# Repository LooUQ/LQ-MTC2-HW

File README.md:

# LooUQ MTC.2 Hardware

Welcome to the hardware and physical parts repository for the LooUQ MTC.2 Ecosystem. Here you will find resources to aid in your implementation of MTC.2 devices in your design/product. Many parts of the LooUQ MTC.2 ecosystem are available as open-source hardware and there design files are available here. There are also drawings for components that can be 3D printed. 

Software developement tooling is found in the LQ-MTC2-SW repository, which is also found on LooUQ's GitHub site.

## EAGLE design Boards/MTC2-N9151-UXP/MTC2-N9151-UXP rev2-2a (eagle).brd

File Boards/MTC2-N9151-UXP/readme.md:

# MTC2-N9151-UXP
The LooUQ MTC2-N9151 UXplor is a development board providing pin access to all of the MTC2-N9151 signals. It allows for software development, flashing and power monitoring via headers located along the right-hand side of the board. SWD access (debug/flashing) is via a standard 5x2 shrouded header. The UXplor also provide N9151 board power from a USB connection. The VIO voltage can be selected via a jumper at either 3.3v or 1.8v (VDD is fixed at 3.7v). The UXplor also includes a RGB LED the is controlled via a TI constant current control chip on the host extension I2C interface.

You can obtain Zephyr devicetree overlays for the Host Extension interface in order to use the RGB LED with the LooUQ driver. These resources, including the driver, are found in the LooUQ GitHub at https://github.com/LooUQ/LooUQ-MTC2-SW.

You can purchase ready-to-use UXplor boards from LooUQ at https://loouq.com/store.

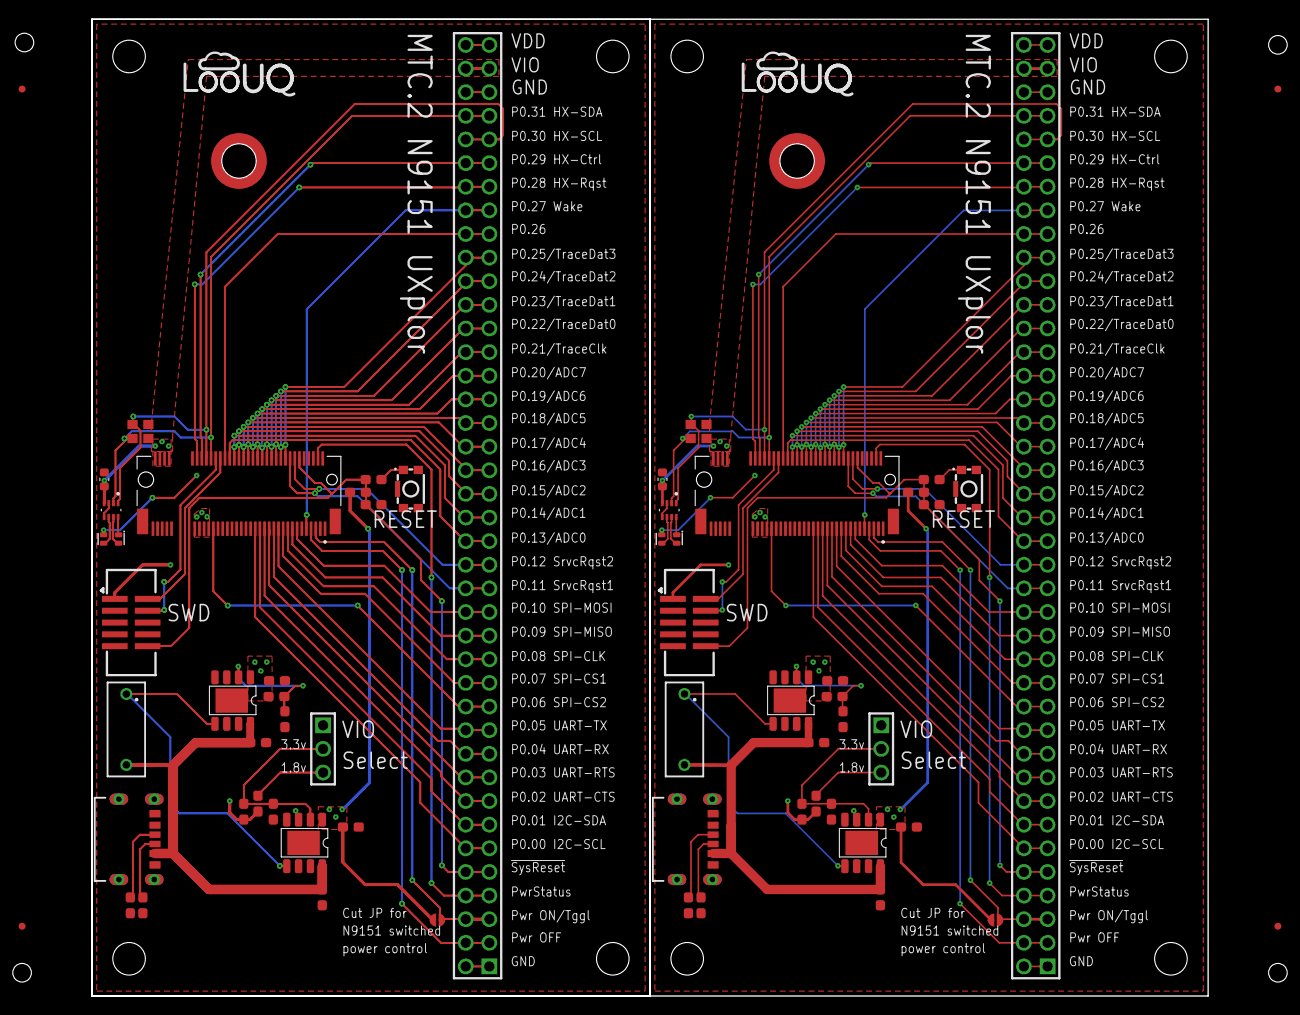
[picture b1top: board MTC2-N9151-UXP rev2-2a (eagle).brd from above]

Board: 2 copper layers, 120.0 x 105.0 mm, 66 parts (0 on the bottom side), 52 nets.

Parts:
C1_1_1, C1_2_1, C2_1_1, C2_2_1, C3_1_1, C3_2_1, C4_1_1, C4_2_1: 4.7uF; CAP_0603
C5_1_1, C5_2_1: 4.7uF; CAP_0603_C5
C6_1_1, C6_2_1: 1uF; CAP_0603_N
D1_1_1, D1_2_1: EAST1616RGBB4; EAST1616RGBB2
FID1, FID2, FID3, FID4: FIDUCIAL; Fiducial
J1_1_1, J1_2_1: CNCTECH 3220-10-0300-00-TR; CnCTech_3220-10-0300-00-TR
J5_1_1, J5_2_1: MTC.2 1-2199230-6 (N9151); TE_1-2199230-6
J8_1_1, J8_2_1: USB4125-GF-A-0190; GCT_USB4125-GF-A-0190_REVA2
J9_1_1, J9_2_1: 90131-0160; HDR-2x40T/2.54x2.54/102x5
J10_1_1, J10_2_1: HDR-1X3T/2.54; HDR-1x3T/2.54/7x2
JP1_1_1, JP1_2_1: CIRCJUMPER-2; Circ-Jumper-2
LG1_1_1, LG1_2_1: LOOUQ LOGO; LooUQ-6mm
MH1_1_1, MH1_2_1: 9774025151R; m.2_standoff
R1_1_1, R1_2_1: 10K; RES_0603
R2_1_1, R2_2_1: 330R; RES_0603_R2
R3_1_1, R3_2_1: 41.7K; RES_0603_R3
R4_1_1, R4_2_1: 62K; RES_0603_R2
R5_1_1, R5_2_1: 73.2K; RES_0603_R5
R6_1_1, R6_2_1: 20K; RES_0603_R6
R7_1_1, R7_2_1: 20K; RES_0603_R5
R8_1_1, R8_2_1, R9_1_1, R9_2_1: 5.1K; RES_0603_R8
R13_1_1, R13_2_1, R14_1_1, R14_2_1: 4.7K; RES_0603_R13
SW1_1_1, SW1_2_1: KMR221GLFS; KMR-2-wG
SW2_1_1, SW2_2_1: 418117270901
U1_1_1, U1_2_1, U2_1_1, U2_2_1: AP7361EA-SPR-13; SO-8EP
U3_1_1, U3_2_1: LP5817DRLR; IC_LP5817DRLR

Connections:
ND_RESETSW: R2_1_1.2, R2_2_1.2, SW1_1_1.1@, SW1_1_1.1@_1, SW1_2_1.1@, SW1_2_1.1@_1
Net_52: J10_1_1.3, J10_2_1.3, R3_1_1.1, R3_2_1.1
Net_Blue: D1_1_1.3, D1_2_1.3, U3_1_1.6, U3_2_1.6
Net_GND: C1_1_1.1, C1_2_1.1, C2_1_1.1, C2_2_1.1, C3_1_1.1, C3_2_1.1, C4_1_1.1, C4_2_1.1, C5_1_1.1, C5_2_1.1, C6_1_1.1, C6_2_1.1, J1_1_1.3, J1_1_1.5, J1_1_1.9, J1_2_1.3, J1_2_1.5, J1_2_1.9, J5_1_1.1, J5_1_1.2, J5_1_1.3, J5_1_1.58, J5_1_1.67, J5_1_1.69, J5_1_1.71, J5_1_1.73, J5_1_1.75, J5_1_1.S1, J5_1_1.S2, J5_2_1.1, J5_2_1.2, J5_2_1.3, J5_2_1.58, J5_2_1.67, J5_2_1.69, J5_2_1.71, J5_2_1.73, J5_2_1.75, J5_2_1.S1, J5_2_1.S2, J8_1_1.A12, J8_1_1.S1, J8_1_1.S2, J8_1_1.S3, J8_1_1.S4, J8_2_1.A12, J8_2_1.S1, J8_2_1.S2, J8_2_1.S3, J8_2_1.S4, J9_1_1.1, J9_1_1.2, J9_1_1.75, J9_1_1.76, J9_2_1.1, J9_2_1.2, J9_2_1.75, J9_2_1.76, R6_1_1.2, R6_2_1.2, R7_1_1.1, R7_2_1.1, R8_1_1.1, R8_2_1.1, R9_1_1.1, R9_2_1.1, SW1_1_1.2@, SW1_1_1.2@_1, SW1_2_1.2@, SW1_2_1.2@_1, U1_1_1.3, U1_2_1.3, U2_1_1.3, U2_2_1.3, U3_1_1.3, U3_1_1.5, U3_2_1.3, U3_2_1.5
Net_Green: D1_1_1.2, D1_2_1.2, U3_1_1.7, U3_2_1.7
Net_PWR-TGL: J5_1_1.5, J5_2_1.5, J9_1_1.5, J9_1_1.6, J9_2_1.5, J9_2_1.6, JP1_1_1.1, JP1_2_1.1
Net_PwrEn: SW2_1_1.1, SW2_2_1.1, U1_1_1.5, U1_2_1.5, U2_1_1.5, U2_2_1.5
Net_Red: D1_1_1.1, D1_2_1.1, U3_1_1.8, U3_2_1.8
Net_SWCLK: J1_1_1.4, J1_2_1.4, J5_1_1.48, J5_2_1.48
Net_SWIO: J1_1_1.2, J1_2_1.2, J5_1_1.46, J5_2_1.46
Net_VBUS: C4_1_1.2, C4_2_1.2, C5_1_1.2, C5_2_1.2, J8_1_1.A9, J8_2_1.A9, SW2_1_1.A1, SW2_2_1.A1, U1_1_1.8, U1_2_1.8, U2_1_1.8, U2_2_1.8
Net_VDD: C2_1_1.2, C2_2_1.2, D1_1_1.4, D1_2_1.4, J5_1_1.51, J5_1_1.53, J5_1_1.55, J5_1_1.57, J5_2_1.51, J5_2_1.53, J5_2_1.55, J5_2_1.57, J9_1_1.79, J9_1_1.80, J9_2_1.79, J9_2_1.80, R5_1_1.2, R5_2_1.2, U1_1_1.1, U1_2_1.1
Net_VIO: C3_1_1.2, C3_2_1.2, C6_1_1.2, C6_2_1.2, J1_1_1.1, J1_2_1.1, J5_1_1.68, J5_1_1.70, J5_1_1.72, J5_1_1.74, J5_2_1.68, J5_2_1.70, J5_2_1.72, J5_2_1.74, J9_1_1.77, J9_1_1.78, J9_2_1.77, J9_2_1.78, JP1_1_1.2, JP1_2_1.2, R1_1_1.2, R1_2_1.2, R3_1_1.2, R3_2_1.2, R4_1_1.2, R4_2_1.2, R13_1_1.2, R13_2_1.2, R14_1_1.2, R14_2_1.2, U2_1_1.1, U2_2_1.1, U3_1_1.4, U3_2_1.4
P0.01_(I2C-SCL): J5_1_1.31, J5_2_1.31, J9_1_1.11, J9_1_1.12, J9_2_1.11, J9_2_1.12
P0.01_(I2C-SDA): J5_1_1.29, J5_2_1.29, J9_1_1.13, J9_1_1.14, J9_2_1.13, J9_2_1.14
P0.02_(UART-CTS): J5_1_1.27, J5_2_1.27, J9_1_1.15, J9_1_1.16, J9_2_1.15, J9_2_1.16
P0.03_(UART-RTS): J5_1_1.25, J5_2_1.25, J9_1_1.17, J9_1_1.18, J9_2_1.17, J9_2_1.18
P0.04_(UART-RX): J5_1_1.23, J5_2_1.23, J9_1_1.19, J9_1_1.20, J9_2_1.19, J9_2_1.20
P0.05_(UART-TX): J5_1_1.21, J5_2_1.21, J9_1_1.21, J9_1_1.22, J9_2_1.21, J9_2_1.22
P0.06_(SPI-CS2): J5_1_1.49, J5_2_1.49, J9_1_1.23, J9_1_1.24, J9_2_1.23, J9_2_1.24
P0.07_(SPI-CS1): J5_1_1.19, J5_2_1.19, J9_1_1.25, J9_1_1.26, J9_2_1.25, J9_2_1.26
P0.08_(SPI-CLK): J5_1_1.17, J5_2_1.17, J9_1_1.27, J9_1_1.28, J9_2_1.27, J9_2_1.28
P0.09_(SPI-MISO): J5_1_1.15, J5_2_1.15, J9_1_1.29, J9_1_1.30, J9_2_1.29, J9_2_1.30
P0.10_(SPI-MOSI): J5_1_1.13, J5_2_1.13, J9_1_1.31, J9_1_1.32, J9_2_1.31, J9_2_1.32
P0.11_(nSrvcRqst1): J5_1_1.16, J5_2_1.16, J9_1_1.33, J9_1_1.34, J9_2_1.33, J9_2_1.34
P0.12_(nSrvcRqst2): J5_1_1.14, J5_2_1.14, J9_1_1.35, J9_1_1.36, J9_2_1.35, J9_2_1.36
P0.13/ADC0: J5_1_1.42, J5_2_1.42, J9_1_1.37, J9_1_1.38, J9_2_1.37, J9_2_1.38
P0.14/ADC1: J5_1_1.40, J5_2_1.40, J9_1_1.39, J9_1_1.40, J9_2_1.39, J9_2_1.40
P0.15/ADC2: J5_1_1.38, J5_2_1.38, J9_1_1.41, J9_1_1.42, J9_2_1.41, J9_2_1.42
P0.16/ADC3: J5_1_1.36, J5_2_1.36, J9_1_1.43, J9_1_1.44, J9_2_1.43, J9_2_1.44
P0.17/ADC4: J5_1_1.34, J5_2_1.34, J9_1_1.45, J9_1_1.46, J9_2_1.45, J9_2_1.46
P0.18/ADC5: J5_1_1.32, J5_2_1.32, J9_1_1.47, J9_1_1.48, J9_2_1.47, J9_2_1.48
P0.19/ADC6: J5_1_1.30, J5_2_1.30, J9_1_1.49, J9_1_1.50, J9_2_1.49, J9_2_1.50
P0.20/ADC7: J5_1_1.28, J5_2_1.28, J9_1_1.51, J9_1_1.52, J9_2_1.51, J9_2_1.52
P0.21/TRACECLK: J5_1_1.26, J5_2_1.26, J9_1_1.53, J9_1_1.54, J9_2_1.53, J9_2_1.54
P0.22/TRACED0: J5_1_1.24, J5_2_1.24, J9_1_1.55, J9_1_1.56, J9_2_1.55, J9_2_1.56
P0.23/TRACED1: J5_1_1.22, J5_2_1.22, J9_1_1.57, J9_1_1.58, J9_2_1.57, J9_2_1.58
P0.24/TRACED2: J5_1_1.20, J5_2_1.20, J9_1_1.59, J9_1_1.60, J9_2_1.59, J9_2_1.60
P0.25/TRACED3: J5_1_1.18, J5_2_1.18, J9_1_1.61, J9_1_1.62, J9_2_1.61, J9_2_1.62
P0.26: J5_1_1.44, J5_2_1.44, J9_1_1.63, J9_1_1.64, J9_2_1.63, J9_2_1.64
P0.27_(Wake): J5_1_1.9, J5_2_1.9, J9_1_1.65, J9_1_1.66, J9_2_1.65, J9_2_1.66
P0.28_(HX-RQST): J5_1_1.56, J5_2_1.56, J9_1_1.67, J9_1_1.68, J9_2_1.67, J9_2_1.68
P0.29_(HX-Ctrl): J5_1_1.54, J5_2_1.54, J9_1_1.69, J9_1_1.70, J9_2_1.69, J9_2_1.70
P0.30_HX-SCL: J5_1_1.52, J5_2_1.52, J9_1_1.71, J9_1_1.72, J9_2_1.71, J9_2_1.72, R14_1_1.1, R14_2_1.1, U3_1_1.1, U3_2_1.1
P0.31_HX-SDA: J5_1_1.50, J5_2_1.50, J9_1_1.73, J9_1_1.74, J9_2_1.73, J9_2_1.74, R13_1_1.1, R13_2_1.1, U3_1_1.2, U3_2_1.2
PUSB_CC1: J8_1_1.A5, J8_2_1.A5, R9_1_1.2, R9_2_1.2
PUSB_CC2: J8_1_1.B5, J8_2_1.B5, R8_1_1.2, R8_2_1.2
PWR-OFF: J5_1_1.7, J5_2_1.7, J9_1_1.3, J9_1_1.4, J9_2_1.3, J9_2_1.4
Status-ON/OFF: J5_1_1.4, J5_2_1.4, J9_1_1.7, J9_1_1.8, J9_2_1.7, J9_2_1.8
VDD_FB: R5_1_1.1, R5_2_1.1, R6_1_1.1, R6_2_1.1, U1_1_1.2, U1_2_1.2
VIO_FB: J10_1_1.2, J10_2_1.2, R4_1_1.1, R4_2_1.1, R7_1_1.2, R7_2_1.2, U2_1_1.2, U2_2_1.2
nSysReset: C1_1_1.2, C1_2_1.2, J1_1_1.10, J1_2_1.10, J5_1_1.12, J5_2_1.12, J9_1_1.9, J9_1_1.10, J9_2_1.9, J9_2_1.10, R1_1_1.1, R1_2_1.1, R2_1_1.1, R2_2_1.1

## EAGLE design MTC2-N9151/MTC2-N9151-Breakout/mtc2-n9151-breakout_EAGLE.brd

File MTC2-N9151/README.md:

# LooUQ MTC2-N9151

The LooUQ MTC2-N9151 is our flagship modem based on the Nordic Semiconductor nRF9151 System-in-Package (SIP) device. Nordic's [documentation](https://docs.nordicsemi.com/category/nrf9151-category) about the nRF9151 SIP is relevant the our MTC2-N9151 modem. LooUQ has done the work to package the nRF9151 SIP into a convenient PCB form to make incorporation into your device as straight forward as possible.

The [MTC.2 Interface Guide](https://drive.google.com/file/d/1XxZAA_1KvOwKZDBlQWn0SYPFL24nAV9U/view?usp=drive_link) discusses the steps to incorporate the N9151 into your product/project. 
* The physical characteristics of mounting the N9151 in your host system
* The electrical requirements needed by the N9151
* The signals to/from the N9151 and it's host

*LooUQ software developement tooling is found in the [LQ-MTC2-SW](https://github.com/LooUQ/LooUQ-MTC2-SW) repository (also found on LooUQ's GitHub site). This includes resources for Nordic Connect SDK like board definition files and sample applications.*

# What You Need
To work with the MTC2-N9151 you will need some things at hand.
* Microsoft [Visual Studio Code](https://code.visualstudio.com/) code editor
* Nordic's [Nordic NRF Connect](https://www.nordicsemi.com/Products/Development-tools/nRF-Connect-for-Desktop?utm_feeditemid=&utm_device=c&utm_term=nrf54l15&utm_source=google&utm_medium=ppc&utm_campaign=nRF54L15&hsa_cam=21894111243&hsa_grp=177111642664&hsa_mt=b&hsa_src=g&hsa_ad=720961843386&hsa_acc=1116845495&hsa_net=adwords&hsa_kw=nrf54l15&hsa_tgt=kwd-2316120203756&hsa_ver=3&gad_source=1&gad_campaignid=21894111243&gbraid=0AAAAADPygHJwnoNPRfWQ0ravOUsDLXLXU&gclid=CjwKCAiA24XJBhBXEiwAXElO39W5oalXI05StjYgUkkjHeaIkVXiZc4hHY8_mm-0arYAEs6eRHNuhhoClUkQAvD_BwE) extension for VS Code
* Nordic's [nRF Connect for Desktop](https://www.nordicsemi.com/Products/Development-tools/nRF-Connect-for-Desktop?utm_feeditemid=&utm_device=c&utm_term=nrf54l15&utm_source=google&utm_medium=ppc&utm_campaign=nRF54L15&hsa_cam=21894111243&hsa_grp=177111642664&hsa_mt=b&hsa_src=g&hsa_ad=720961843386&hsa_acc=1116845495&hsa_net=adwords&hsa_kw=nrf54l15&hsa_tgt=kwd-2316120203756&hsa_ver=3&gad_source=1&gad_campaignid=21894111243&gbraid=0AAAAADPygHJwnoNPRfWQ0ravOUsDLXLXU&gclid=CjwKCAiA24XJBhBXEiwAXElO39W5oalXI05StjYgUkkjHeaIkVXiZc4hHY8_mm-0arYAEs6eRHNuhhoClUkQAvD_BwE) (optional, but highly recommended)
* A SWD debugging probe (Segger J-Link recommended)
* A MTC.2 host providing connections and power (see LooUQ's offerings below, available in our online store)
* A MTC2-N9151 *(of course you will need one or more of these)*
* Antenna(s) 
    * Depending on your use case you will need a cellular antenna for LTE/DECT-NR+ and a GNSS antenna for GNSS/GPS location determination.

## Using LooUQ Development hosts
LooUQ has two development hosts available to make getting started with the MTC2-N9151 a straight forward process: the MTC2-N9151-BRK (breakout board) and the MTC2-N9151-UXP (UXplor host). With either of these two boards, you can get started developing applications for the N9151. They are physically the same size and have identical peripheral header pin configurations.

### MTC2-N9151-Breakout
The N9151 breakout board is simply that, a breakout, exposing all the signals to/from the MTC2-N9151 modem device. Connections for external power, nRF9151 reset, SWD (flash/debug) and all peripheral pins (GPIO, I2C, SPI, UART, etc.). The breakout is designed to be simple and stay out of the way, providing only the essentials for flashing and debugging your N9151 applications.

### MTC2-N9151-UXplor
The N9151 UXplor is the breakout PLUS handy other functionality. The UXplor has a USB connector that sources power via integrated regulators. There is a VDD regulator delivery 3.8v and a VIO regulator that can be set for 3.3v or 1.8v. There is also a RGB LED indicator, the RBG controller is from TI and is I2C-connected. LooUQ provides a driver for LED controller, which is available in the LooUQ-MTC2-SW software repository.

## Creating MTC2-N9151 Applications
If you are new to ***Nordic nRF Connect*** consider investing time in completing one or more of the fine online courses at the [Nordic Developer Academy](https://academy.nordicsemi.com/). If you already have nRF Connect development experience, head over to the [software repository](https://github.com/LooUQ/LooUQ-MTC2-SW) and check out the information there. We have board definitions, samples, and driver code ready for your use. 

## Creating Your Own MTC2-N9151 Host 
LooUQ uses DipTrace as our PCB design suite. It has a complete set of tools for schematic creation, PCB layout, and maintaining component libraries. For information about DipTrace and how to use it see...[Get Diptrace](https://diptrace.com/). LooUQ has been using DipTrace as our electronics design tool since 2016 and we are proud to proclaim it's virtues: reasonable cost, wide support, comprehensive set of tooling; give it a try.

Given that there are multiple tools out there for PCB design/develoment, LooUQ is sharing our open-hardware designs in both DipTrace and Eagle formats. Eagle is a widely supported format for schematic and PCB board layouts. Both of the host boards above are available in the Boards folder of this repository. Depending on your needs either could be a good starting point for integration into your project.

Nordic documentation about the nRF9151 SIP applies to the LooUQ MTC2-9151; all limits should be observed. The MTC2-N9151 will draw slightly more power depending on operating state. GNSS has power draw for either the on-board LNA chip and optionally the external LNA power injection circuit. The N9151 also has 2 LEDs (power-green, network-blue), which can be individually disabled by cutting a jumper. LooUQ can deliver the MTC2-N9151 with custom LNA or LED configurations (note MOQ is required).

### Interfacing to the N9151
* Physical layout
* Power
    * VDD: 3.0v - 5.5v (LooUQ has observed that when VDD is above 4.5v, a VIO of 1.8v has issues)
    * VIO: 1.7v to 3.6v
    * The UXplor VDD is 3.8v and VIO is selectable at 3.3v or 1.8v
* Flash/debug requires connectivity to the 2 SWD pins (both the Breakout and UXplor expose these signals to a 10-pin Cortex header)
* Both LTE/DECT and GNSS antennas are directly connected to the MTC2-N9151 via U.FL connectors

**Host Physical Board Layout**
The physical connection between the MTC2-N9151 and the host PCB is accomplished with 3 parts in the configuration below.
* TE 1-2199230-6 (M.2 Key-M)
* Wurth 9774025151R (M2.5 stand-off, soldered)
* 2.5M x 8mm hex head bolt (fully-threaded, course)

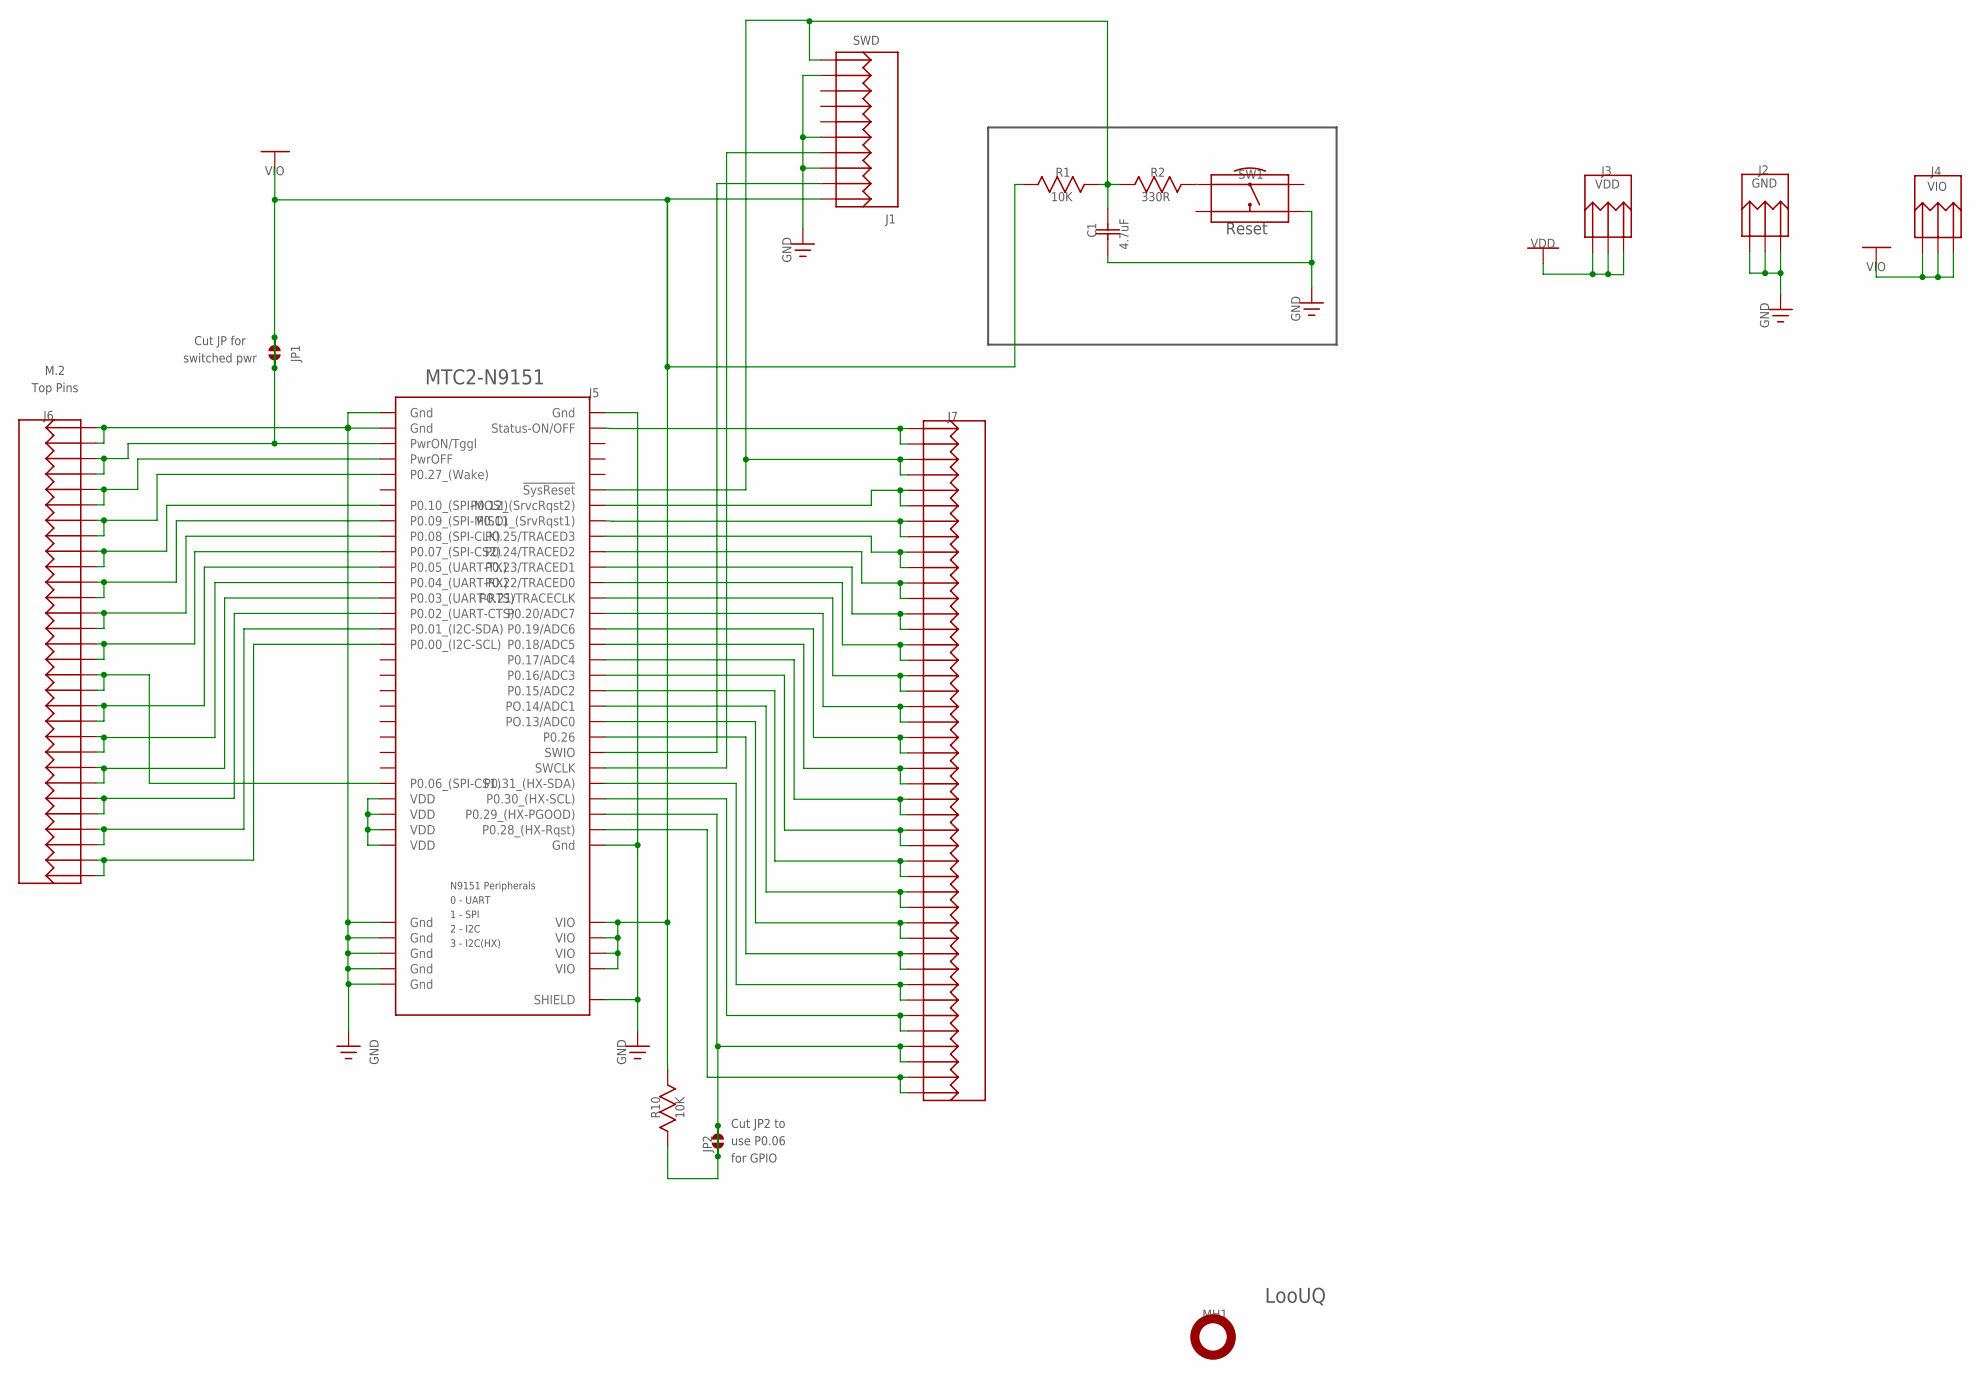
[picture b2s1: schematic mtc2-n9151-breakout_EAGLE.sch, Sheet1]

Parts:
C1: 4.7uF; CAP_0603
J1: CNCTECH_3220-10-0300-00-TR
J2, J3, J4: 644456-3; HDR-1X3T/2.54/7X2
J5: MTC.2_1-2199230-6_(N9151); TE_1-2199230-6
J6: DEV_J6; HDR-2X15T/2.54X2.54/38X5
J7: DEV_J7; HDR-2X22T/2.54X2.54/56X5
JP1, JP2: CIRCJUMPER-2; CIRC-JUMPER-2
LG1: LOOUQ_LOGO; LOOUQ-6MM
MH1: 9774025151R; M.2_STANDOFF
R1, R10: 10K; RES_0603
R2: 330R; RES_0603
SW1: KMR221GLFS; KMR-2-WG

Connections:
ND_RESETSW: R2.2, SW1.1@, SW1.1@_1 (1)
Net_GND: C1.1, J1.3, J1.5, J1.9, J2.1, J2.2, J2.3, J5.1 (Gnd), J5.2 (Gnd), J5.3 (Gnd), J5.58 (Gnd), J5.67 (Gnd), J5.69 (Gnd), J5.71 (Gnd), J5.73 (Gnd), J5.75 (Gnd), J5.S1 (SHIELD), J5.S2 (SHIELD), J6.1, J6.2, SW1.2@, SW1.2@_1 (2)
Net_SWCLK: J1.4, J5.48 (SWCLK)
Net_SWIO: J1.2, J5.46 (SWIO)
Net_VDD: J3.1, J3.2, J3.3, J5.51 (VDD), J5.53 (VDD), J5.55 (VDD), J5.57 (VDD)
Net_VIO: J1.1, J4.1, J4.2, J4.3, J5.5 (PwrON/Tggl), J5.68 (VIO), J5.70 (VIO), J5.72 (VIO), J5.74 (VIO), J6.3, J6.4, JP1.1, JP1.2, R1.2, R10.2
P0.00_I2C-SCL: J5.31 (P0.00_(I2C-SCL)), J6.29, J6.30
P0.01_I2C-SDA: J5.29 (P0.01_(I2C-SDA)), J6.27, J6.28
P0.02_UART-CTS: J5.27 (P0.02_(UART-CTS)), J6.25, J6.26
P0.03_UART-RTS: J5.25 (P0.03_(UART-RTS)), J6.23, J6.24
P0.04_UART-RX: J5.23 (P0.04_(UART-RX)), J6.21, J6.22
P0.05_UART-TX: J5.21 (P0.05_(UART-TX)), J6.19, J6.20
P0.06_SPI-CS1: J5.49 (P0.06_(SPI-CS1)), J6.17, J6.18
P0.08_SPI-CLK: J5.17 (P0.08_(SPI-CLK)), J6.13, J6.14
P0.09_SPI-MISO: J5.15 (P0.09_(SPI-MISO)), J6.11, J6.12
P0.10_SPI-MOSI: J5.13 (P0.10_(SPI-MOSI)), J6.9, J6.10
P0.11_SrvcRqst1: J5.16 (P0.11_(SrvRqst1)), J7.37, J7.38
P0.12_SrvcRqst2: J5.14 (P0.12_(SrvcRqst2)), J7.39, J7.40
P0.13_ADC0: J5.42 (PO.13/ADC0), J7.11, J7.12
P0.14_ADC1: J5.40 (PO.14/ADC1), J7.13, J7.14
P0.15_ADC2: J5.38 (P0.15/ADC2), J7.15, J7.16
P0.16_ADC3: J5.36 (P0.16/ADC3), J7.17, J7.18
P0.17_ADC4: J5.34 (P0.17/ADC4), J7.19, J7.20
P0.18_ADC5: J5.32 (P0.18/ADC5), J7.21, J7.22
P0.19_ADC6: J5.30 (P0.19/ADC6), J7.23, J7.24
P0.20_ADC7: J5.28 (P0.20/ADC7), J7.25, J7.26
P0.21_TraceClk: J5.26 (P0.21/TRACECLK), J7.27, J7.28
P0.22_TraceD0: J5.24 (P0.22/TRACED0), J7.29, J7.30
P0.23_TraceD1: J5.22 (P0.23/TRACED1), J7.31, J7.32
P0.24_TraceD2: J5.20 (P0.24/TRACED2), J7.33, J7.34
P0.25_TraceD3: J5.18 (P0.25/TRACED3), J7.35, J7.36
P0.26: J5.44 (P0.26), J7.9, J7.10
P0.27_WAKE: J5.9 (P0.27_(Wake)), J6.7, J6.8
P0.28_(HX-Rqst): J5.56 (P0.28_(HX-Rqst)), J7.1, J7.2
P0.29_(HX-PGOOD): J5.54 (P0.29_(HX-PGOOD)), J7.3, J7.4, JP2.1, JP2.2, R10.1
P0.30_HX-SCL: J5.52 (P0.30_(HX-SCL)), J7.5, J7.6
P0.31_HX-SDA: J5.50 (P0.31_(HX-SDA)), J7.7, J7.8
PwrOFF: J5.7 (PwrOFF), J6.5, J6.6
PwrStatus: J5.4 (Status-ON/OFF), J7.43, J7.44
nSysReset: C1.2, J1.10, J5.12 (!SysReset), J7.41, J7.42, R1.1, R2.1
p0.07_SPI-CS2: J5.19 (P0.07_(SPI-CS2)), J6.15, J6.16

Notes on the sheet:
GND
VDD
VIO
Reset
M.2 Top Pins
Cut JP for switched pwr
Cut JP2 to use P0.06 for GPIO
SWD
4.7uF
N9151 Peripherals 0 - UART 1 - SPI 2 - I2C 3 - I2C(HX)
MTC2-N9151
JP1
JP2
LooUQ
MH1
10K
330R
R10
SW1

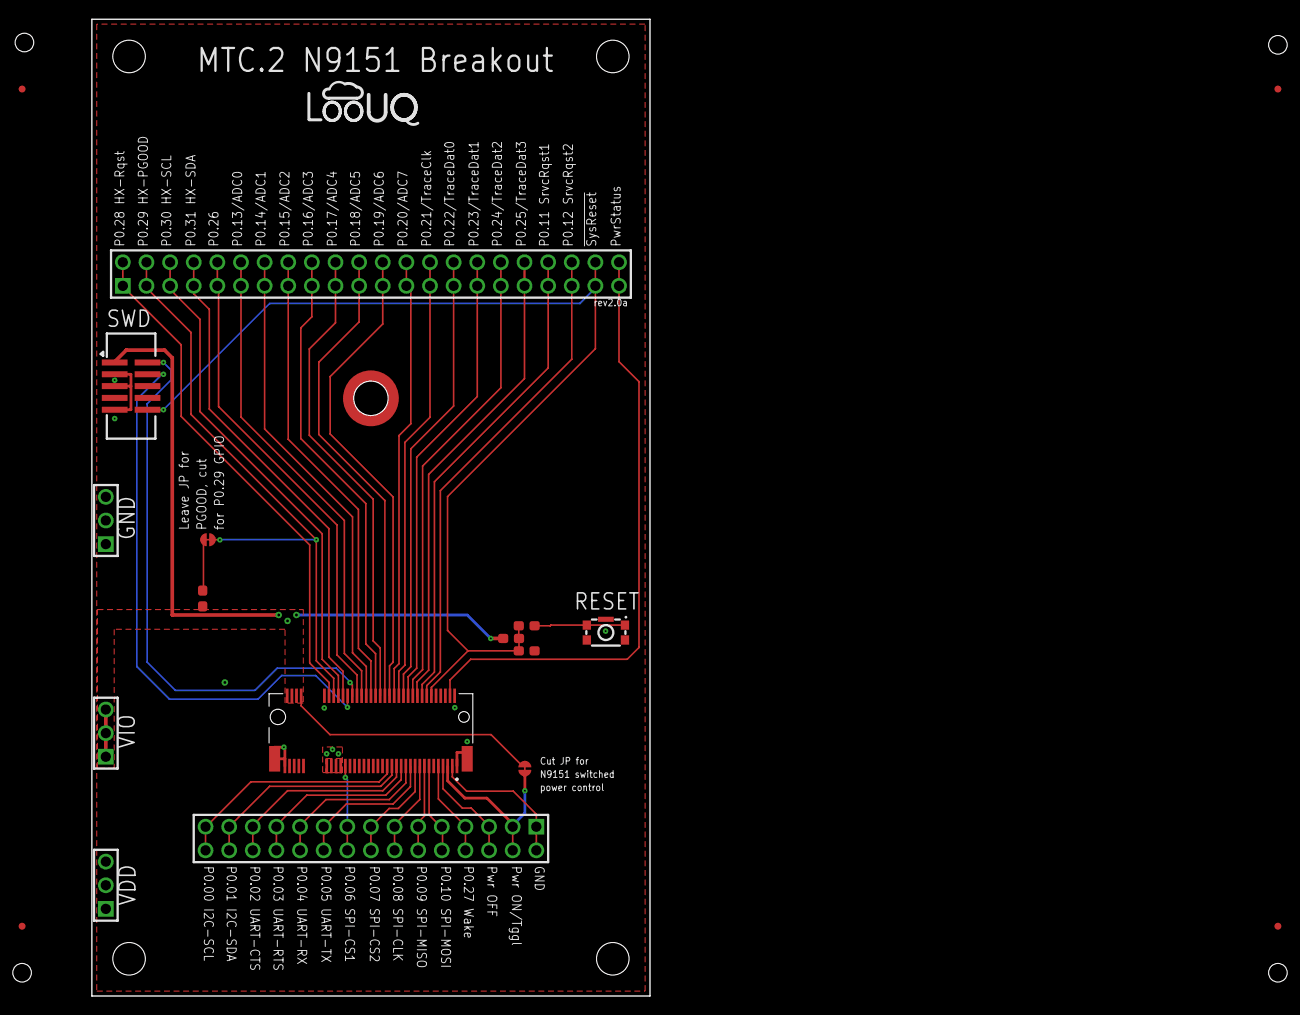
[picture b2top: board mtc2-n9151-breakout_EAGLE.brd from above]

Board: 2 copper layers, 60.0 x 105.0 mm, 20 parts (0 on the bottom side), 41 nets.

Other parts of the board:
FID1, FID2, FID3, FID4: FIDUCIAL; Fiducial

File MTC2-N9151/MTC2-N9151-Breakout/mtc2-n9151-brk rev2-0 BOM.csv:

"#","RefDes","Qty","Manufacturer","Name","Value","Alternate","Pattern","Mount","Side","Description"
"1","C1","1","Samsung","CL10A475KP8NNNC","4.7uF","","CAP_0603","","",""
"2","J1","1","CnCTech","CnCTech 3220-10-0300-00-TR","","","CnCTech 3220-10-0300-00-TR","","",""
"3","J2","1","TE Connectivity","644456-3","","","HDR-1x3T/2.54/7x2","TH","",""
"4","J3","1","TE Connectivity","644456-3","","","HDR-1x3T/2.54/7x2","TH","",""
"5","J4","1","TE Connectivity","644456-3","","","HDR-1x3T/2.54/7x2","TH","",""
"6","J5","1","TE Connectivity","MTC.2 1-2199230-6 (N9151)","","","TE_1-2199230-6","","","
67 Position Female Connector M.2 (NGFF) Mini Card Gold 0.020 (0.50mm) Black
"
"7","J6","1","","","","","HDR-2x15T/2.54x2.54/38x5","TH","",""
"8","J7","1","","","","","HDR-2x22T/2.54x2.54/56x5","TH","",""
"9","JP1","1","","CircJumper-2","","","Circ-Jumper-2","TR","",""
"10","JP2","1","","CircJumper-2","","","Circ-Jumper-2","TR","",""
"11","LG1","1","PCB","LooUQ Logo","","","LooUQ-6mm","SLK","","LooUQ logo silk"
"12","MH1","1","Wurth","9774025151R","","","m.2 standoff","","",""
"13","R1","1","Stackpole","RNCP0603FTD10K0","10K","","RES_0603","","",""
"14","R2","1","Walsin Technology","WR06X3300FTL","330R","","RES_0603","","",""
"15","R10","1","Stackpole","RNCP0603FTD10K0","10K","","RES_0603","","","RES 10K OHM 1% 1/8W 0603"
"16","SW1","1","C&K","KMR221GLFS","","","KMR-2-wG","","","Tactile Switch SPST-NO Top Actuated Surface Mount, GndPin, 300gf"

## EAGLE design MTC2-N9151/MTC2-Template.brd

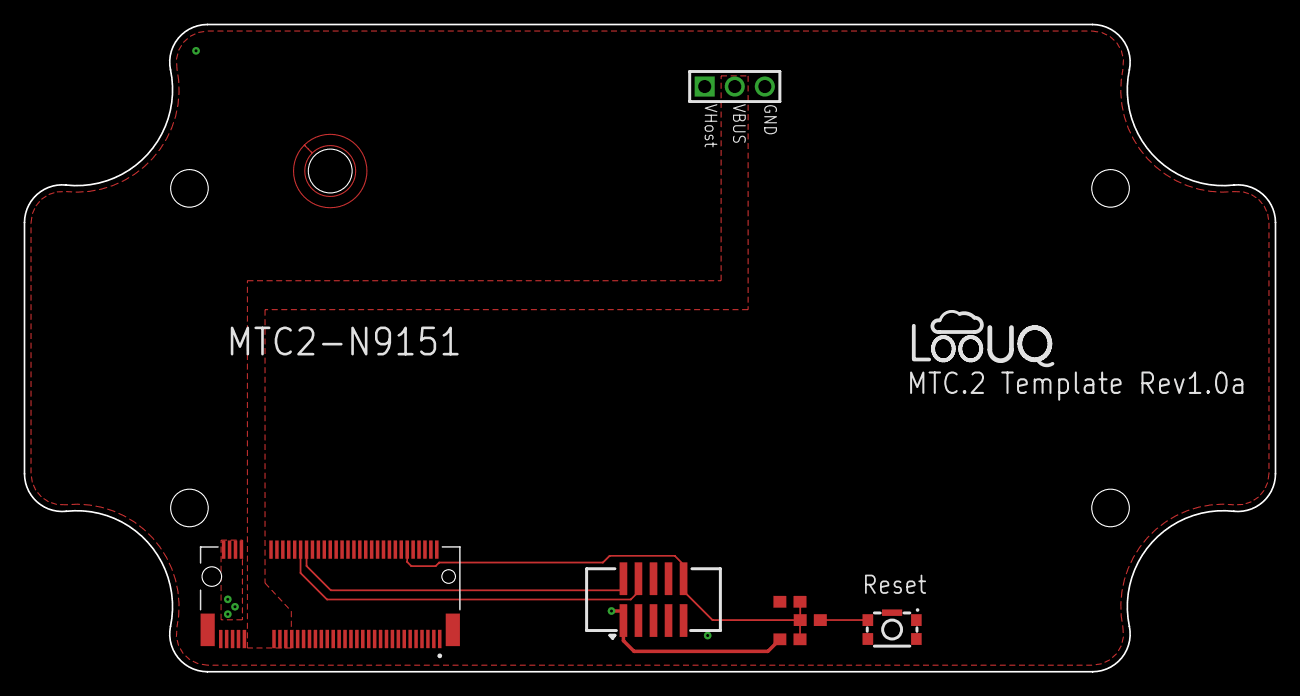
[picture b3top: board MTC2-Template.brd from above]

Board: 2 copper layers, 105.6 x 54.7 mm, 8 parts (0 on the bottom side), 7 nets.

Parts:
C1: 100nF; CAP_0603
J1: 1-2199230-6; TE_1-2199230-6
J3: BD125-10-A-0305-0580-L-B; CnCTech_3220-10-0300-00-TR
J4: 3PIN T/H HEADER; HDR-1x3T/2.54/7x2
LG1: LOOUQ LOGO; LooUQ-6mm
R1: 10K; RES_0603
R2: 330R; RES_0603_R2
SW1: KMR231GLFS; KMR-2-wG

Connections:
ND_RESET: C1.2, J1.12, J3.10, R1.1, R2.1
ND_RESETSW: R2.2, SW1.1@, SW1.1@_1
ND_SWD_CLK: J1.48, J3.4
ND_SWD_IO: J1.46, J3.2
Net_GND: C1.1, J1.1, J1.2, J1.58, J1.75, J1.S1, J1.S2, J3.3, J3.9, J4.3, SW1.2@, SW1.2@_1
Net_VBus: J1.51, J1.53, J1.55, J1.57, J4.2
Net_VHOST: J1.68, J1.70, J1.72, J1.74, J3.1, J4.1, R1.2

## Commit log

2025-11-19 Update from local
2025-11-19 Added N9151-BRK files
2025-11-20 Add implementation resources
2025-11-22 Update readme and reorganize hw locations
2026-01-10 Updated BRK and UXP board files
